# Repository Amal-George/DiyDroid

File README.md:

# DiyDroid
ESP32 based differential toy car for beginners.

## Components

1. ESP32 Devkit
2. Motor Driver - L293D
3. Capacitive touch switches
4. WS2812b LEDs
5. TP4056 Battery Charger Module

## Version: 0.1
> Added PCB Design (KiCad 7.0)

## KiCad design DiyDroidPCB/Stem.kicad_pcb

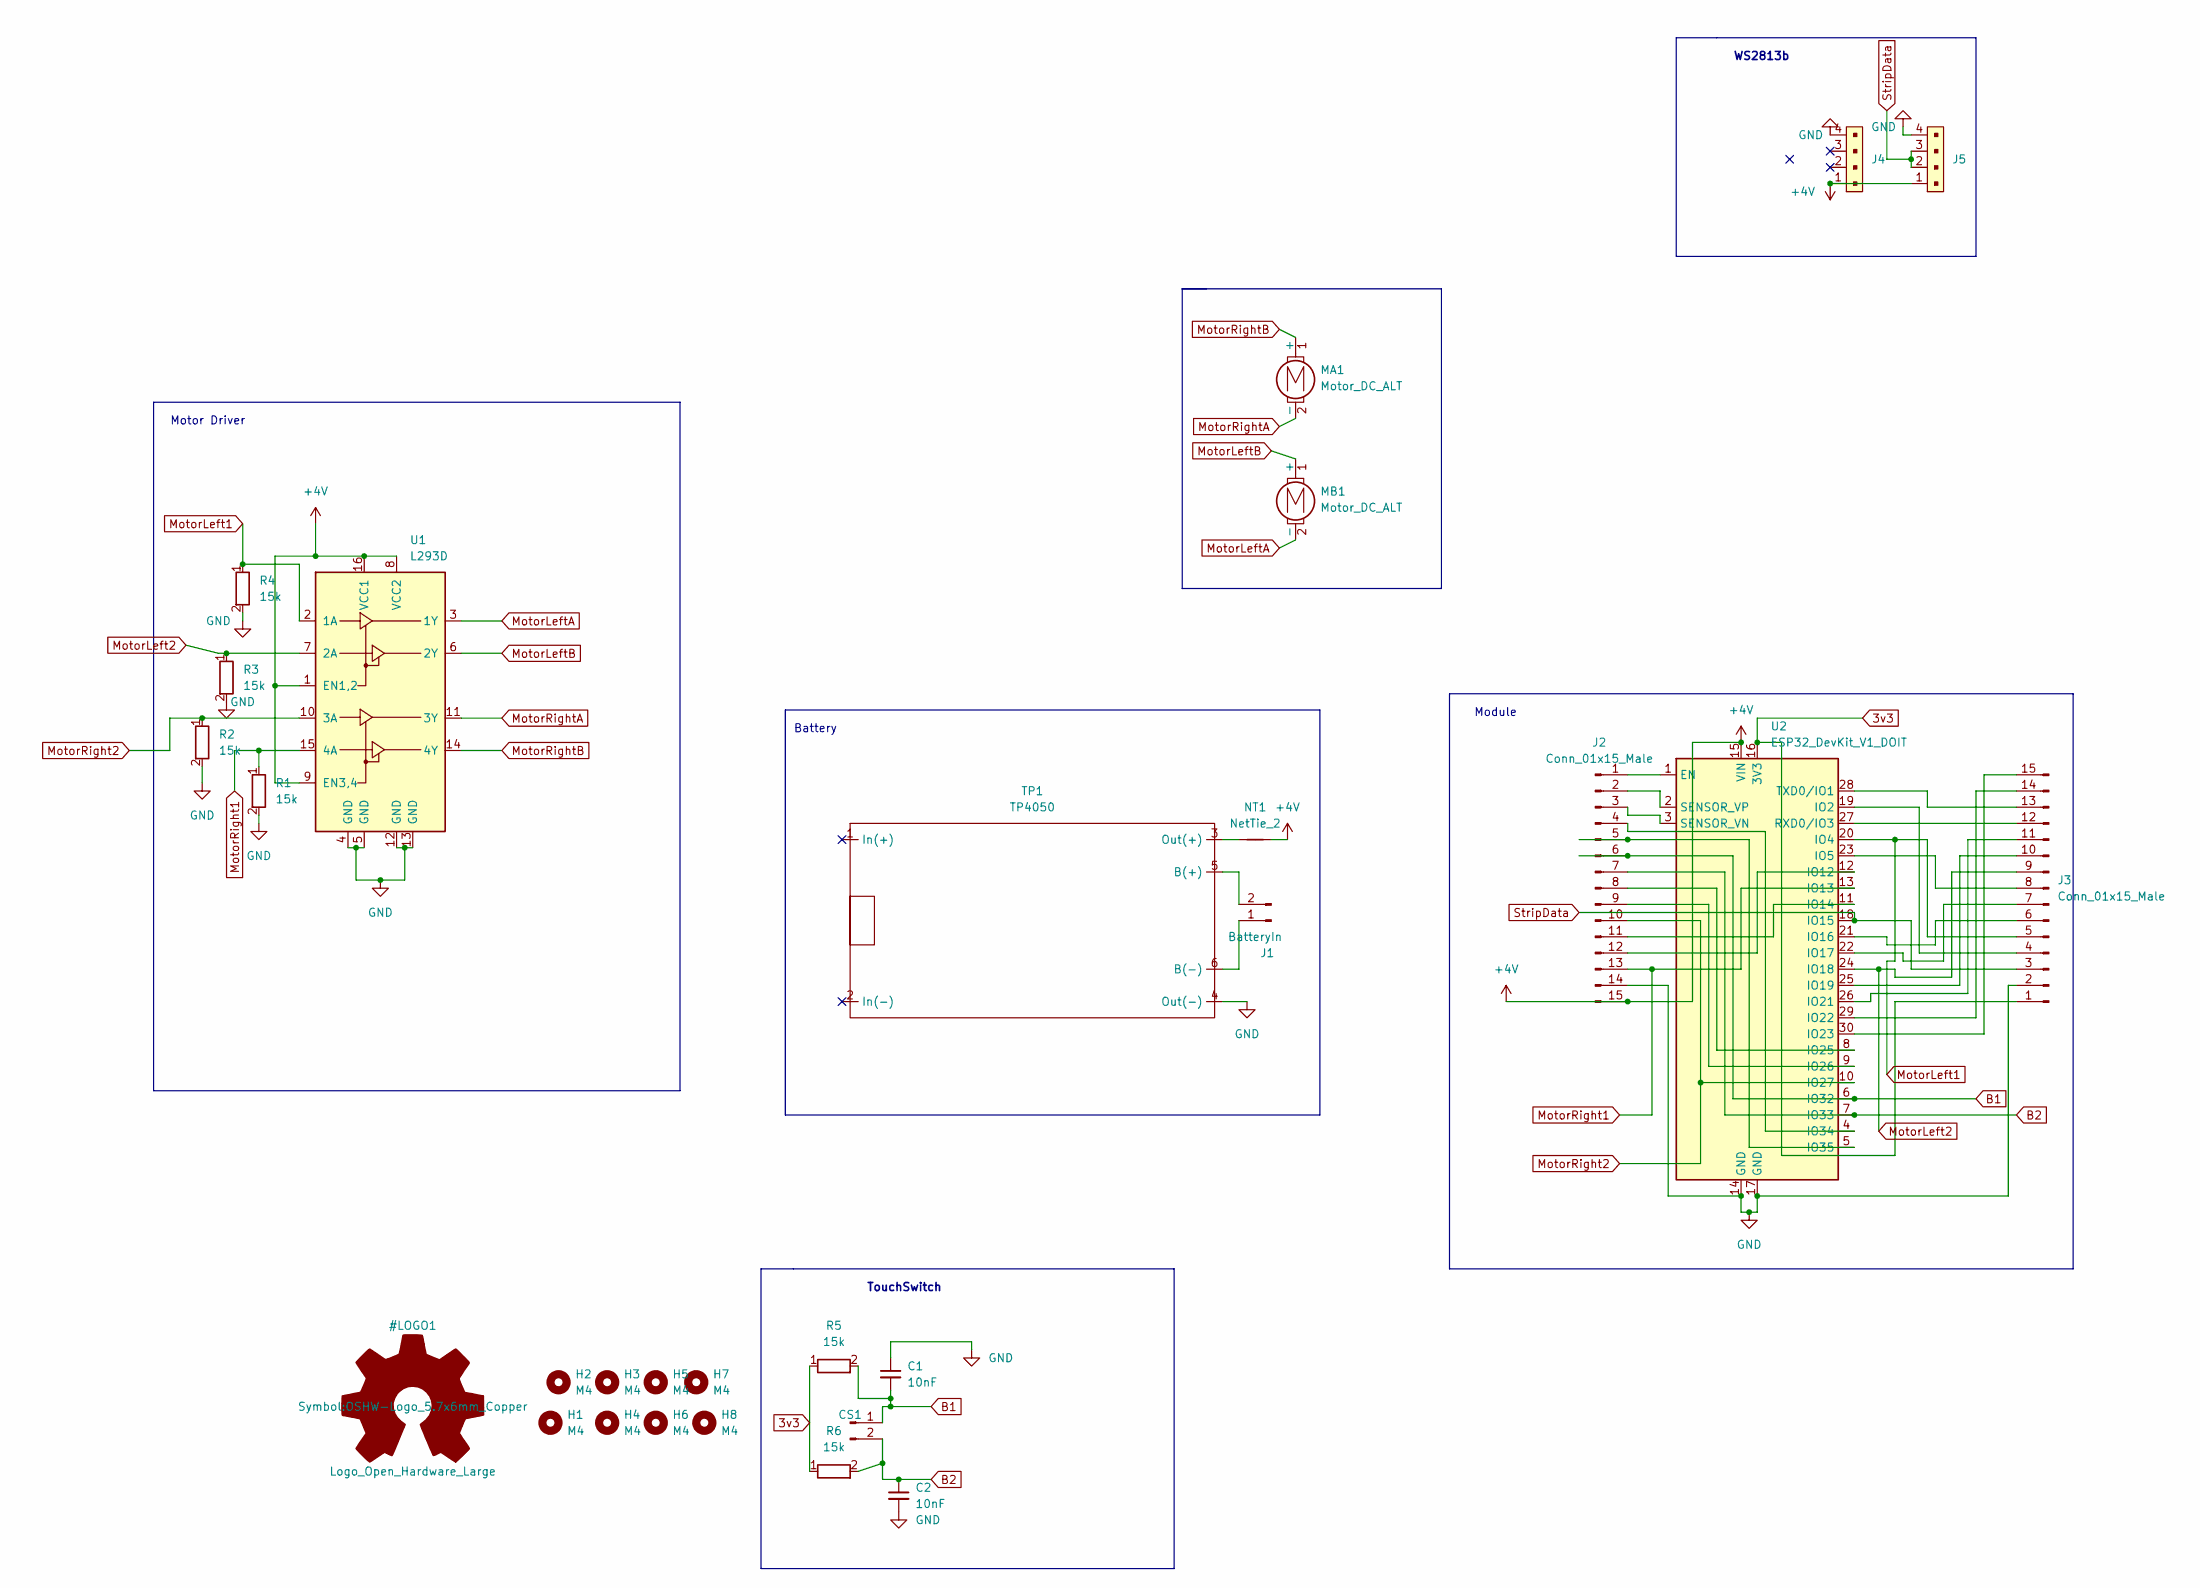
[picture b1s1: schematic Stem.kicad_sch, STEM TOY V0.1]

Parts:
C1, C2: 10nF; C_1206_3216Metric
CS1: Conn_01x02_Male; CapacitiveTouchPad
H1, H2, H3, H4, H5, H6, H7, H8: M4; MountingHole_4.3mm_M4
J1: BatteryIn; JST_XH_B2B-XH-A_1x02_P2.50mm_Vertical
J2, J3: Conn_01x15_Male; PinHeader_1x15_P2.54mm_Vertical
J4, J5: 0022232041; PinHeader_1x4_P2.54mm_Drill1.02mm; MPN 0022232041; Digi-Key_PN WM4202-ND
MA1: Motor_DC_ALT; JST_XH_B2B-XH-A_1x02_P2.50mm_Vertical
MB1: Motor_DC_ALT; JST_XH_B2B-XH-A_1x02_P2.50mm_Vertical
NT1: NetTie_2; PinHeader_1x02_P2.54mm_Vertical
R1, R2, R3, R4, R5, R6: 15k; R_1206_3216Metric
TP1: TP4050; TP4056-18650
U1: L293D; DIP-16_W7.62mm
U2: ESP32_DevKit_V1_DOIT; esp32_devkit_v1_doit

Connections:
3v3: J3.1, R5.1, R6.1, U2.16 (3V3)
+4V: J2.15, J4.1, J5.1, NT1.2, U1.1 (EN1,2), U1.8 (VCC2), U1.9 (EN3,4), U1.16 (VCC1), U2.15 (VIN)
B1: C1.2, CS1.1, J2.6, R5.2, U2.6 (IO32)
B2: C2.1, CS1.2, J2.7, R6.2, U2.7 (IO33)
GND: C1.1, C2.2, J2.14, J3.2, J4.4, J5.4, R1.2, R2.2, R3.2, R4.2, TP1.4 (Out(-)), U1.4 (GND), U1.5 (GND), U1.12 (GND), U1.13 (GND), U2.14 (GND), U2.17 (GND)
MotorLeft1: J3.5, R4.1, U1.2 (1A), U2.20 (IO4)
MotorLeft2: J3.9, R3.1, U1.7 (2A), U2.24 (IO18)
MotorLeftA: MB1.2 (-), U1.3 (1Y); also elsewhere on the board
MotorLeftB: MB1.1 (+), U1.6 (2Y); also elsewhere on the board
MotorRight1: J2.13, R1.1, U1.15 (4A), U2.13 (IO13)
MotorRight2: J2.10, R2.1, U1.10 (3A), U2.10 (IO27)
MotorRightA: MA1.2 (-), U1.11 (3Y); also elsewhere on the board
MotorRightB: MA1.1 (+), U1.14 (4Y); also elsewhere on the board
unnamed: J1.1, TP1.6 (B(-))
unnamed: J1.2, TP1.5 (B(+))
unnamed: J2.2, U2.2 (SENSOR_VP)
unnamed: J2.3, U2.3 (SENSOR_VN)
unnamed: J2.4, U2.4 (IO34)
unnamed: J2.5, U2.5 (IO35)
unnamed: J2.8, U2.8 (IO25)
unnamed: J2.9, U2.9 (IO26)
unnamed: J2.11, U2.11 (IO14)
unnamed: J2.12, U2.12 (IO12)
unnamed: J3.6, U2.21 (IO16)
unnamed: J3.8, U2.23 (IO5)
unnamed: J3.10, U2.25 (IO19)
unnamed: J3.12, U2.27 (RXD0/IO3)
unnamed: J3.13, U2.28 (TXD0/IO1)
unnamed: J3.14, U2.29 (IO22)
unnamed: NT1.1, TP1.3 (Out(+))
unnamed: J2.1, U2.1 (EN)
unnamed: J3.4, U2.19 (IO2)
unnamed: J3.7, U2.22 (IO17)
unnamed: J3.11, U2.26 (IO21)
unnamed: J3.15, U2.30 (IO23)
StripData: J3.3, J5.2, J5.3, U2.18 (IO15)

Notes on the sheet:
Module
Battery
WS2813b
Motor Driver
TouchSwitch

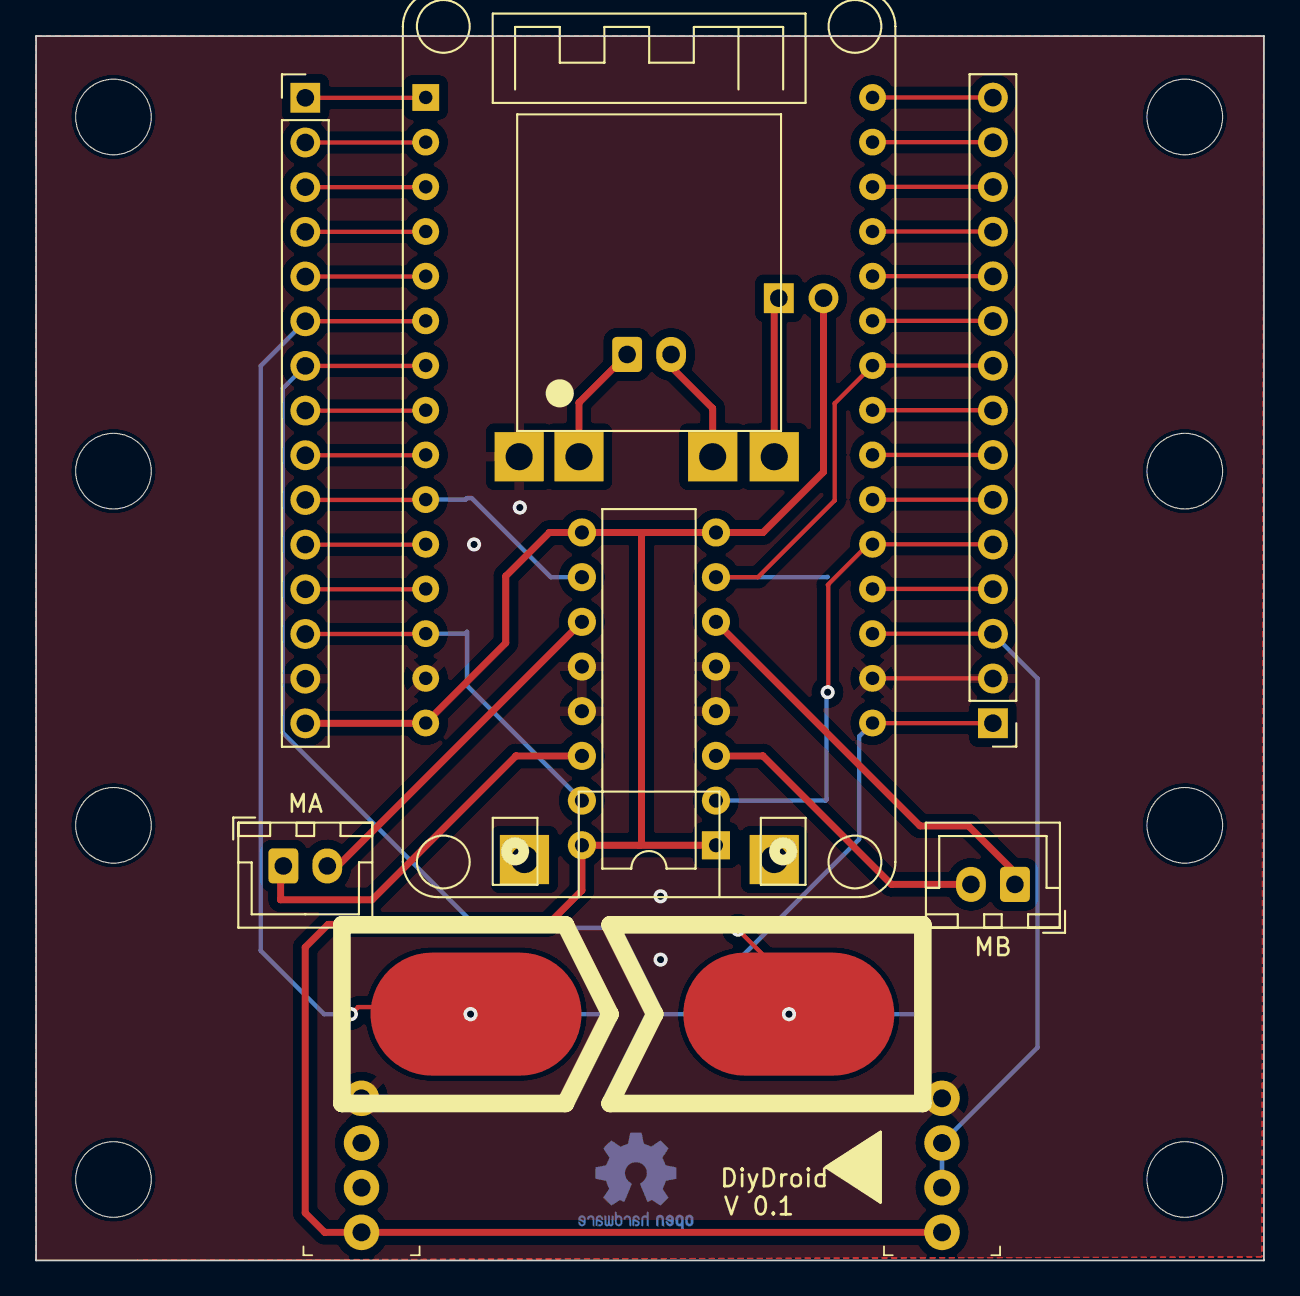
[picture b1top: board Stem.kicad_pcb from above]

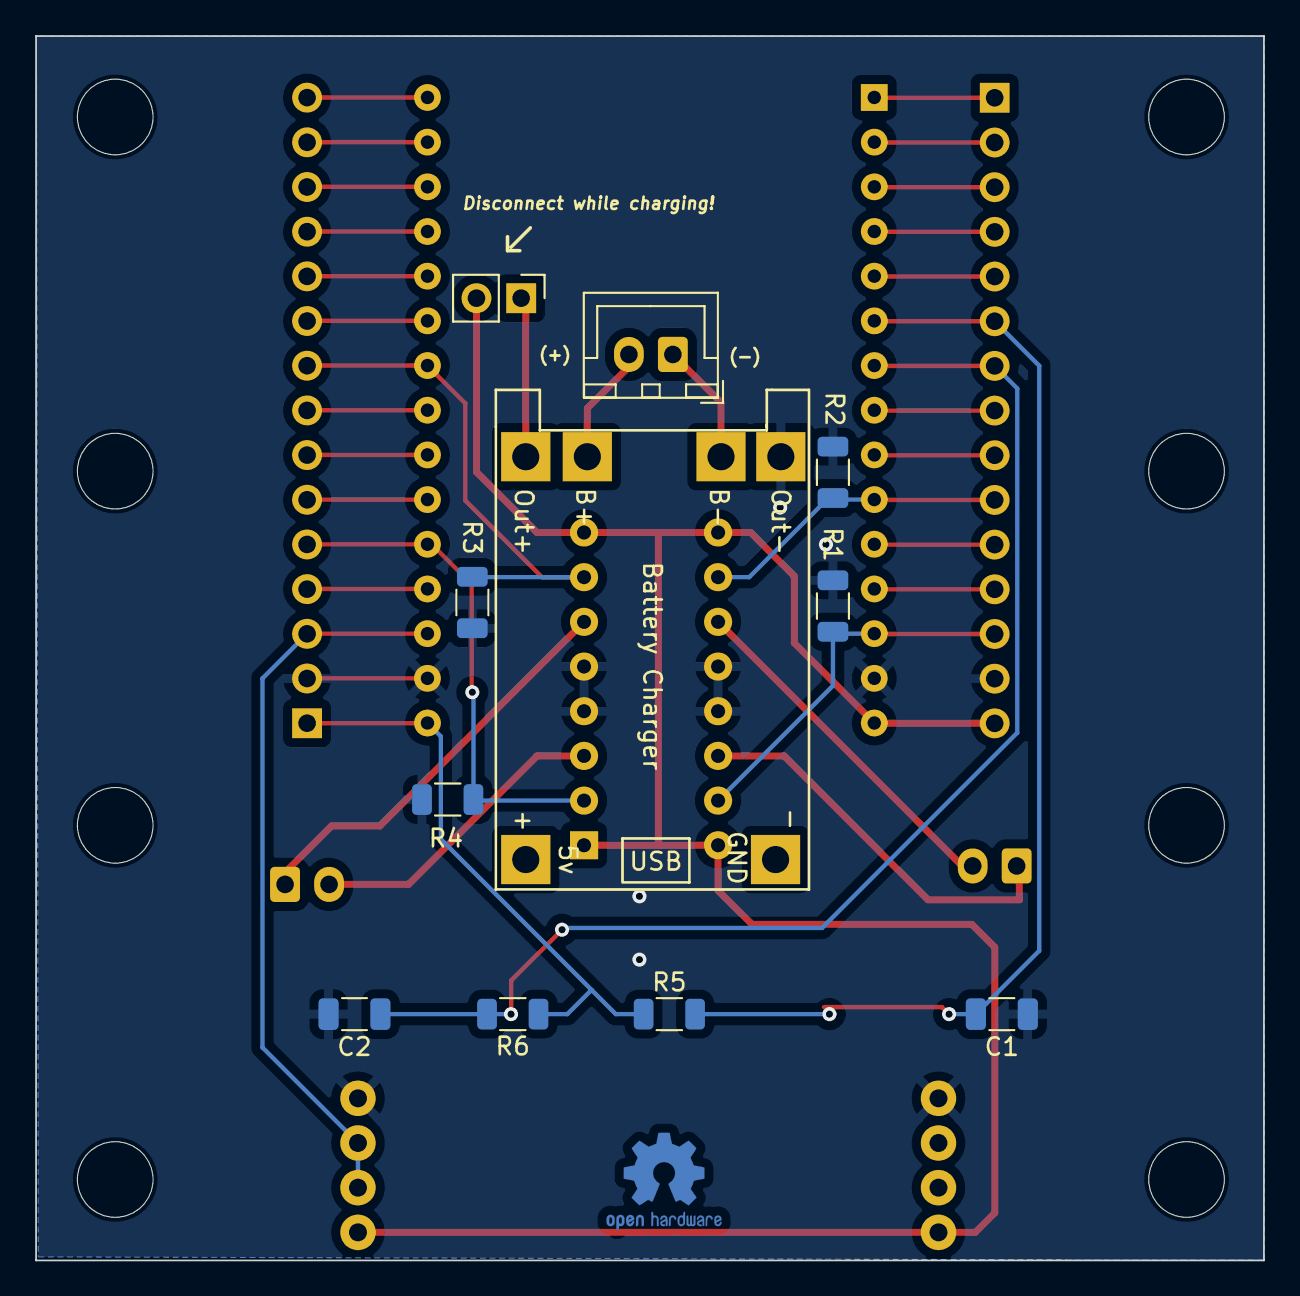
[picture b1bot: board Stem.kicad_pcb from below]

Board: 2 copper layers, 69.8 x 69.6 mm, 28 parts (11 on the bottom side), 36 nets.

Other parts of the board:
MA: Motor_DC_ALT; JST_XH_B2B-XH-A_1x02_P2.50mm_Vertical
MB: Motor_DC_ALT; JST_XH_B2B-XH-A_1x02_P2.50mm_Vertical

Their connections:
MotorLeftA: MB.2 (-); also elsewhere on the board
MotorLeftB: MB.1 (+); also elsewhere on the board
MotorRightA: MA.2 (-); also elsewhere on the board
MotorRightB: MA.1 (+); also elsewhere on the board

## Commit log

2023-03-13 V 0.1
